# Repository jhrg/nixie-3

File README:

An alternative to the ShiftRegister74HC595 library is the builtin
shiftOut() function that is part of the Arduino IDE/libraries.

``` 
byte leds = 0;
bitSet(leds, i);

/*
 * updateShiftRegister() - This function sets the latchPin to low,
 * then calls the Arduino function 'shiftOut' to shift out contents
 * of variable 'leds' in the shift register before putting the 'latchPin' high again.
 */
void updateShiftRegister() {
    digitalWrite(latchPin, LOW);
    shiftOut(dataPin, clockPin, LSBFIRST, leds);
    digitalWrite(latchPin, HIGH);
}
```

Faster pin reads. See https://forum.arduino.cc/t/digital-read-write-pinmode-fast-execution/89116

// --- PIN MODE: OUTPUT  --- 

  DDRD |= _BV (0); // pinMode (0, OUTPUT);
  DDRD |= _BV (1); // pinMode (1, OUTPUT);
  DDRD |= _BV (2); // pinMode (2, OUTPUT);
  DDRD |= _BV (3); // pinMode (3, OUTPUT);
  DDRD |= _BV (4); // pinMode (4, OUTPUT);
  DDRD |= _BV (5); // pinMode (5, OUTPUT);
  DDRD |= _BV (6); // pinMode (6, OUTPUT);
  DDRD |= _BV (7); // pinMode (7, OUTPUT);
  DDRB |= _BV (0); // pinMode (8, OUTPUT);
  DDRB |= _BV (1); // pinMode (9, OUTPUT);
  DDRB |= _BV (2); // pinMode (10, OUTPUT);
  DDRB |= _BV (3); // pinMode (11, OUTPUT);
  DDRB |= _BV (4); // pinMode (12, OUTPUT);
  DDRB |= _BV (5); // pinMode (13, OUTPUT);
  DDRC |= _BV (0); // pinMode (A0, OUTPUT);
  DDRC |= _BV (1); // pinMode (A1, OUTPUT);
  DDRC |= _BV (2); // pinMode (A2, OUTPUT);
  DDRC |= _BV (3); // pinMode (A3, OUTPUT);
  DDRC |= _BV (4); // pinMode (A4, OUTPUT);
  DDRC |= _BV (5); // pinMode (A5, OUTPUT);

// --- PIN MODE: INPUT  --- 

  DDRD &= ~_BV (0); // pinMode (0, INPUT);
  DDRD &= ~_BV (1); // pinMode (1, INPUT);
  DDRD &= ~_BV (2); // pinMode (2, INPUT);
  DDRD &= ~_BV (3); // pinMode (3, INPUT);
  DDRD &= ~_BV (4); // pinMode (4, INPUT);
  DDRD &= ~_BV (5); // pinMode (5, INPUT);
  DDRD &= ~_BV (6); // pinMode (6, INPUT);
  DDRD &= ~_BV (7); // pinMode (7, INPUT);
  DDRB &= ~_BV (0); // pinMode (8, INPUT);
  DDRB &= ~_BV (1); // pinMode (9, INPUT);
  DDRB &= ~_BV (2); // pinMode (10, INPUT);
  DDRB &= ~_BV (3); // pinMode (11, INPUT);
  DDRB &= ~_BV (4); // pinMode (12, INPUT);
  DDRB &= ~_BV (5); // pinMode (13, INPUT);
  DDRC &= ~_BV (0); // pinMode (A0, INPUT);
  DDRC &= ~_BV (1); // pinMode (A1, INPUT);
  DDRC &= ~_BV (2); // pinMode (A2, INPUT);
  DDRC &= ~_BV (3); // pinMode (A3, INPUT);
  DDRC &= ~_BV (4); // pinMode (A4, INPUT);
  DDRC &= ~_BV (5); // pinMode (A5, INPUT);

// --- DIGITAL WRITE: HIGH  --- 

  PORTD |= _BV (0); // digitalWrite (0, HIGH);
  PORTD |= _BV (1); // digitalWrite (1, HIGH);
  PORTD |= _BV (2); // digitalWrite (2, HIGH);
  PORTD |= _BV (3); // digitalWrite (3, HIGH);
  PORTD |= _BV (4); // digitalWrite (4, HIGH);
  PORTD |= _BV (5); // digitalWrite (5, HIGH);
  PORTD |= _BV (6); // digitalWrite (6, HIGH);
  PORTD |= _BV (7); // digitalWrite (7, HIGH);

  PORTB |= _BV (0); // digitalWrite (8, HIGH);
  PORTB |= _BV (1); // digitalWrite (9, HIGH);
  PORTB |= _BV (2); // digitalWrite (10, HIGH);
  PORTB |= _BV (3); // digitalWrite (11, HIGH);
  PORTB |= _BV (4); // digitalWrite (12, HIGH);
  PORTB |= _BV (5); // digitalWrite (13, HIGH);

  PORTC |= _BV (0); // digitalWrite (A0, HIGH);
  PORTC |= _BV (1); // digitalWrite (A1, HIGH);
  PORTC |= _BV (2); // digitalWrite (A2, HIGH);
  PORTC |= _BV (3); // digitalWrite (A3, HIGH);
  PORTC |= _BV (4); // digitalWrite (A4, HIGH);
  PORTC |= _BV (5); // digitalWrite (A5, HIGH);

// --- DIGITAL WRITE: LOW  --- 

  PORTD &= ~_BV (0); // digitalWrite (0, LOW);
  PORTD &= ~_BV (1); // digitalWrite (1, LOW);
  PORTD &= ~_BV (2); // digitalWrite (2, LOW);
  PORTD &= ~_BV (3); // digitalWrite (3, LOW);
  PORTD &= ~_BV (4); // digitalWrite (4, LOW);
  PORTD &= ~_BV (5); // digitalWrite (5, LOW);
  PORTD &= ~_BV (6); // digitalWrite (6, LOW);
  PORTD &= ~_BV (7); // digitalWrite (7, LOW);

  PORTB &= ~_BV (0); // digitalWrite (8, LOW);
  PORTB &= ~_BV (1); // digitalWrite (9, LOW);
  PORTB &= ~_BV (2); // digitalWrite (10, LOW);
  PORTB &= ~_BV (3); // digitalWrite (11, LOW);
  PORTB &= ~_BV (4); // digitalWrite (12, LOW);
  PORTB &= ~_BV (5); // digitalWrite (13, LOW);
  
  PORTC &= ~_BV (0); // digitalWrite (A0, LOW);
  PORTC &= ~_BV (1); // digitalWrite (A1, LOW);
  PORTC &= ~_BV (2); // digitalWrite (A2, LOW);
  PORTC &= ~_BV (3); // digitalWrite (A3, LOW);
  PORTC &= ~_BV (4); // digitalWrite (A4, LOW);
  PORTC &= ~_BV (5); // digitalWrite (A5, LOW);

// --- DIGITAL READ  --- 

  x = (PIND & _BV (0)) == 0; // digitalRead (0);
  x = (PIND & _BV (1)) == 0; // digitalRead (1);
  x = (PIND & _BV (2)) == 0; // digitalRead (2);
  x = (PIND & _BV (3)) == 0; // digitalRead (3);
  x = (PIND & _BV (4)) == 0; // digitalRead (4);
  x = (PIND & _BV (5)) == 0; // digitalRead (5);
  x = (PIND & _BV (6)) == 0; // digitalRead (6);
  x = (PIND & _BV (7)) == 0; // digitalRead (7);
  x = (PINB & _BV (0)) == 0; // digitalRead (8);
  x = (PINB & _BV (1)) == 0; // digitalRead (9);
  x = (PINB & _BV (2)) == 0; // digitalRead (10);
  x = (PINB & _BV (3)) == 0; // digitalRead (11);
  x = (PINB & _BV (4)) == 0; // digitalRead (12);
  x = (PINB & _BV (5)) == 0; // digitalRead (13);
  x = (PINC & _BV (0)) == 0; // digitalRead (A0);
  x = (PINC & _BV (1)) == 0; // digitalRead (A1);
  x = (PINC & _BV (2)) == 0; // digitalRead (A2);
  x = (PINC & _BV (3)) == 0; // digitalRead (A3);
  x = (PINC & _BV (4)) == 0; // digitalRead (A4);
  x = (PINC & _BV (5)) == 0; // digitalRead (A5);

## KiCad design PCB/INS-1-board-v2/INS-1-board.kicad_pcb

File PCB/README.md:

## Ideal Project Structure

    my_kicad_project/
    ├── my_project.kicad_sch
    ├── my_project.kicad_pcb
    ├── my_project.kicad_pro
    ├── footprints/
    │   └── custom_footprint.pretty/
    └── symbols/
        └── custom_symbol.kicad_sym

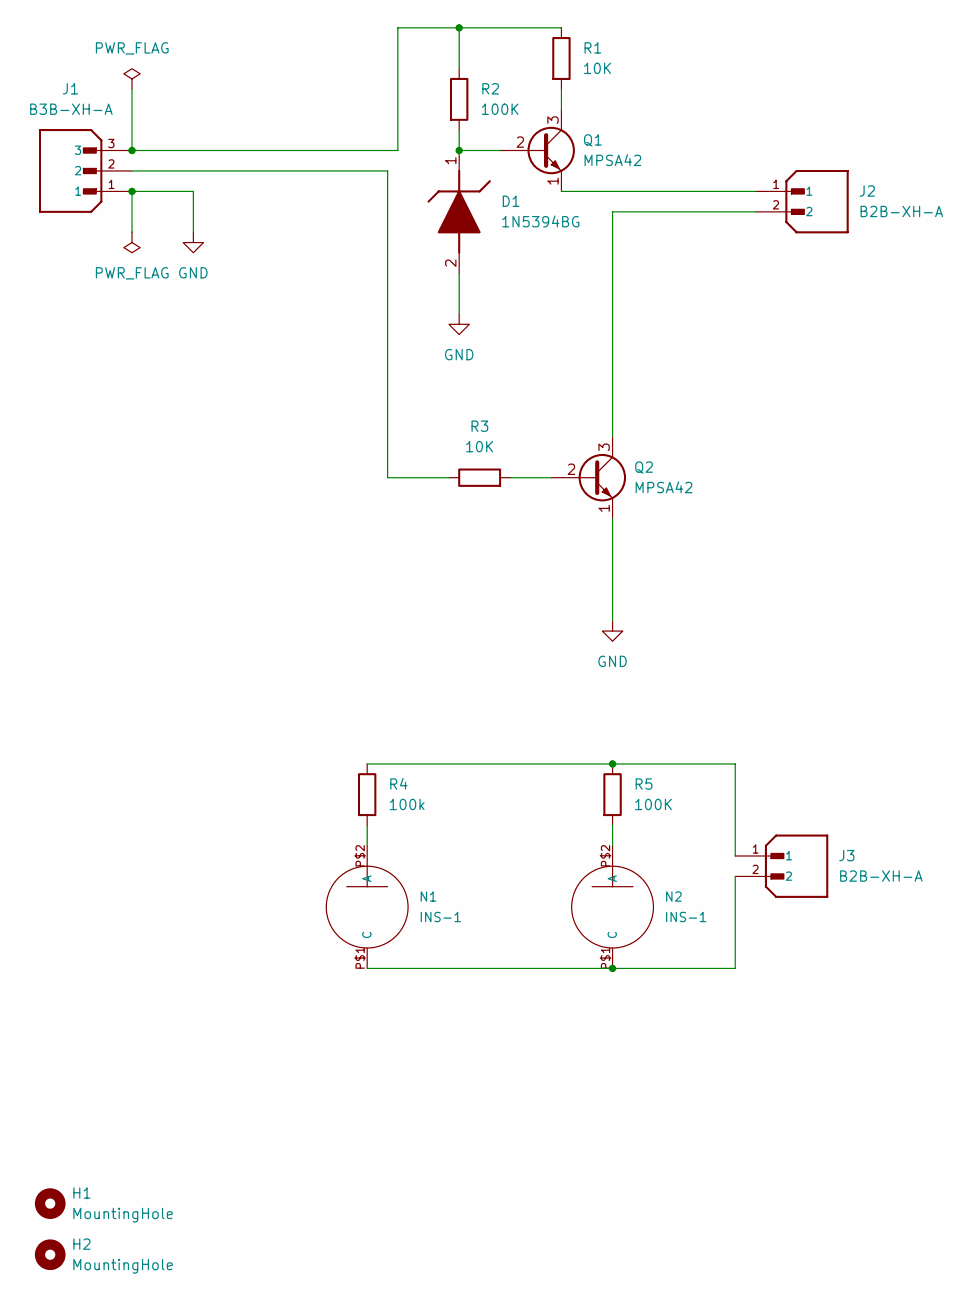
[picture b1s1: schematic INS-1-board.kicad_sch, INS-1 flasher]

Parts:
D1: 1N5394BG; DIOAD2260W109L864D349; Manufacturer_Part_Number 1N5374BG
H1, H2: MountingHole; MountingHole_2.7mm
J1: B3B-XH-A; JST_B3B-XH-A; PARTREV 7/4/21
J2, J3: B2B-XH-A; JST_B2B-XH-A; PARTREV N/A
N1, N2: INS-1; mynixies-INS-1
Q1, Q2: MPSA42; TO-92L_HandSolder
R1, R3: 10K; R_Axial_DIN0207_L6.3mm_D2.5mm_P7.62mm_Horizontal
R2, R5: 100K; R_Axial_DIN0207_L6.3mm_D2.5mm_P7.62mm_Horizontal
R4: 100k; R_Axial_DIN0207_L6.3mm_D2.5mm_P7.62mm_Horizontal

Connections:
GND: D1.2 (A), J1.1, Q2.1 (E)
unnamed: D1.1 (K), Q1.2 (B), R2.2
unnamed: J1.2, R3.1
unnamed: J1.3, R1.1, R2.1
unnamed: J3.1, R4.1, R5.1
unnamed: N1.P$2 (A), R4.2
unnamed: J3.2, N1.P$1 (C), N2.P$1 (C)
unnamed: N2.P$2 (A), R5.2
unnamed: Q1.3 (C), R1.2
unnamed: J2.1, Q1.1 (E)
unnamed: Q2.2 (B), R3.2
unnamed: J2.2, Q2.3 (C)

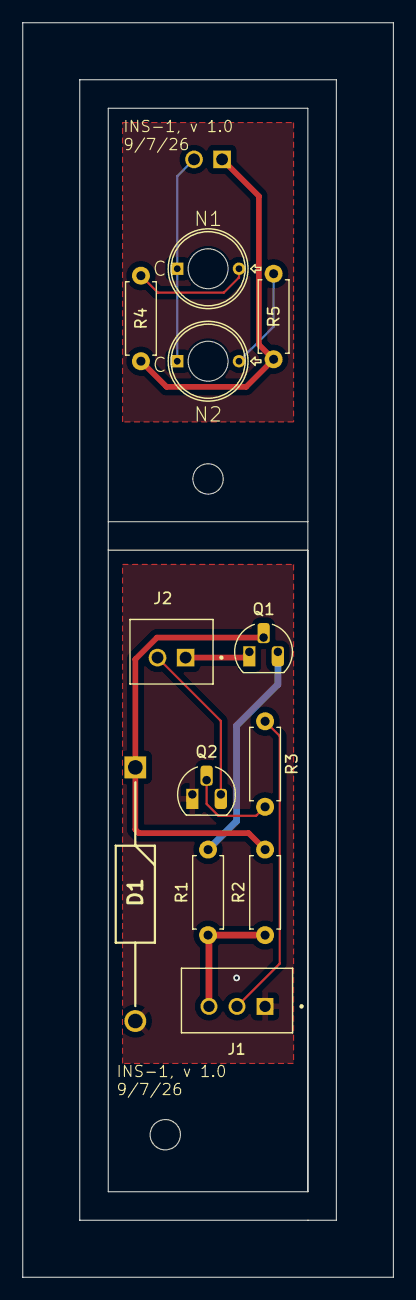
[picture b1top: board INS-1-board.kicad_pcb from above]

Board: 2 copper layers, 33.0 x 111.8 mm, 15 parts (1 on the bottom side), 12 nets.

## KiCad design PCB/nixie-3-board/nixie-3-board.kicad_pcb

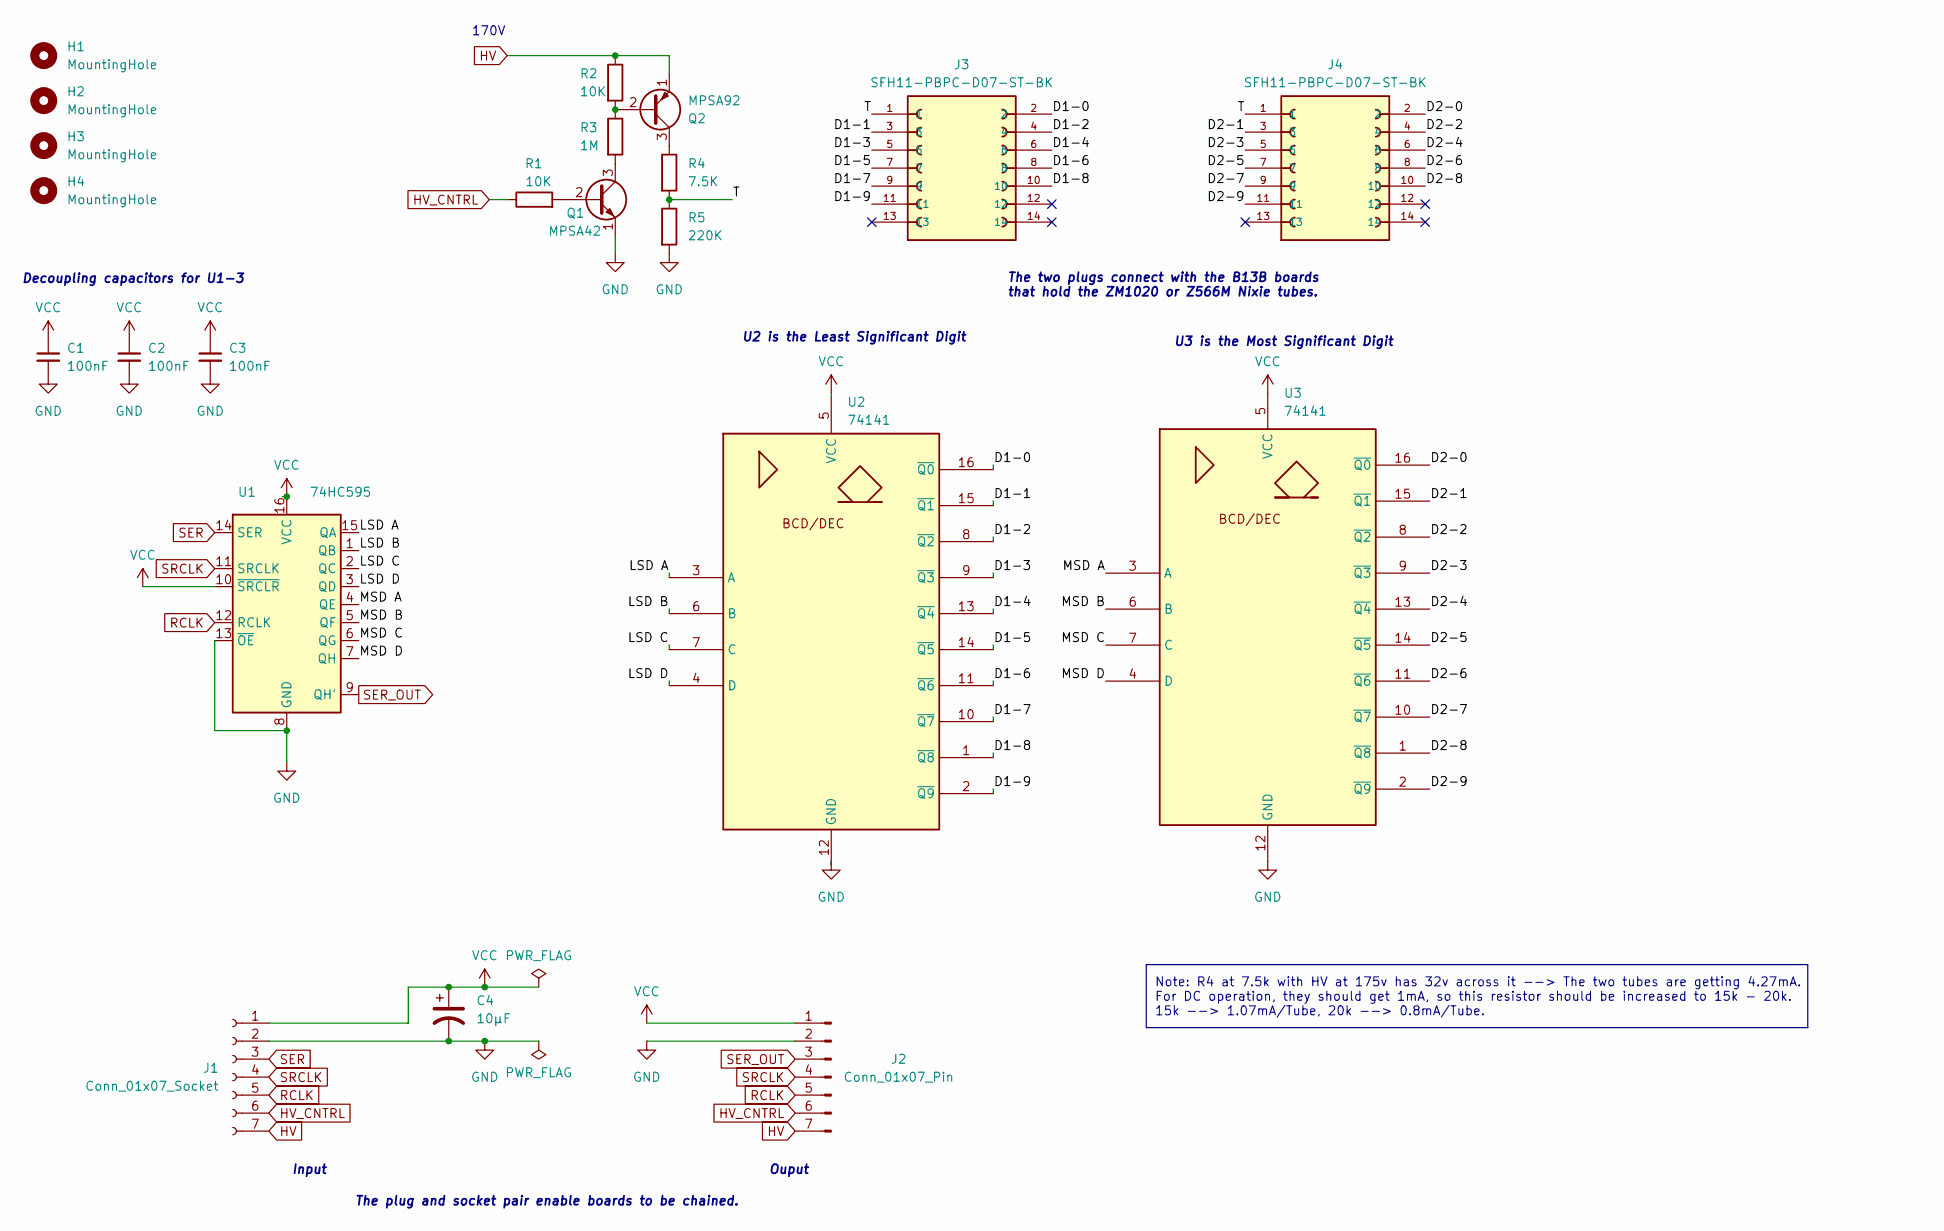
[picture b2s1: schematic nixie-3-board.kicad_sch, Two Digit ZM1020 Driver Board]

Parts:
C1, C2, C3: 100nF; K104Z15Y5VF5TL2_VIS
C4: 10µF; U1-E_NCH
H1, H2, H3, H4: MountingHole; MountingHole_2.7mm_M2.5_DIN965
J1: Conn_01x07_Socket; PinSocket_1x07_P2.54mm_Horizontal
J2: Conn_01x07_Pin; PinHeader_1x07_P2.54mm_Horizontal
J3, J4: SFH11-PBPC-D07-ST-BK; SULLINS_SFH11-PBPC-D07-ST-BK; PARTREV J
Q1: MPSA42; TO-92_HandSolder
Q2: MPSA92; TO-92_HandSolder
R1, R2: 10K; R_Axial_DIN0207_L6.3mm_D2.5mm_P7.62mm_Horizontal
R3: 1M; R_Axial_DIN0207_L6.3mm_D2.5mm_P7.62mm_Horizontal
R4: 7.5K; R_Axial_DIN0207_L6.3mm_D2.5mm_P7.62mm_Horizontal
R5: 220K; R_Axial_DIN0207_L6.3mm_D2.5mm_P7.62mm_Horizontal
U1: 74HC595; DIP-16_W7.62mm_Socket
U2, U3: 74141; DIP-16_W7.62mm_Socket

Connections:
/D1-0: J3.2, U2.16 (~Q0)
/D1-1: J3.3, U2.15 (~Q1)
/D1-2: J3.4, U2.8 (~Q2)
/D1-3: J3.5, U2.9 (~Q3)
/D1-4: J3.6, U2.13 (~Q4)
/D1-5: J3.7, U2.14 (~Q5)
/D1-6: J3.8, U2.11 (~Q6)
/D1-7: J3.9, U2.10 (~Q7)
/D1-8: J3.10, U2.1 (~Q8)
/D1-9: J3.11, U2.2 (~Q9)
/D2-0: J4.2, U3.16 (~Q0)
/D2-1: J4.3, U3.15 (~Q1)
/D2-2: J4.4, U3.8 (~Q2)
/D2-3: J4.5, U3.9 (~Q3)
/D2-4: J4.6, U3.13 (~Q4)
/D2-5: J4.7, U3.14 (~Q5)
/D2-6: J4.8, U3.11 (~Q6)
/D2-7: J4.9, U3.10 (~Q7)
/D2-8: J4.10, U3.1 (~Q8)
/D2-9: J4.11, U3.2 (~Q9)
/LSD A: U1.15 (QA), U2.3 (A)
/LSD B: U1.1 (QB), U2.6 (B)
/LSD C: U1.2 (QC), U2.7 (C)
/LSD D: U1.3 (QD), U2.4 (D)
/MSD A: U1.4 (QE), U3.3 (A)
/MSD B: U1.5 (QF), U3.6 (B)
/MSD C: U1.6 (QG), U3.7 (C)
/MSD D: U1.7 (QH), U3.4 (D)
/T: J3.1, J4.1, R4.2, R5.1
GND: C1.2, C2.2, C3.2, C4.2, J1.2, J2.2, Q1.1 (E), R5.2, U1.8 (GND), U1.13 (~OE), U2.12 (GND), U3.12 (GND)
HV: J1.7, J2.7, Q2.1 (E), R2.1
HV_CNTRL: J1.6, J2.6, R1.1
unnamed: Q1.2 (B), R1.2
unnamed: Q1.3 (C), R3.2
unnamed: Q2.2 (B), R2.2, R3.1
unnamed: Q2.3 (C), R4.1
RCLK: J1.5, J2.5, U1.12 (RCLK)
SER: J1.3, U1.14 (SER)
SER_OUT: J2.3, U1.9 (QH')
SRCLK: J1.4, J2.4, U1.11 (SRCLK)
VCC: C1.1, C2.1, C3.1, C4.1, J1.1, J2.1, U1.10 (~SRCLR), U1.16 (VCC), U2.5 (VCC), U3.5 (VCC)

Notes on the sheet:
U2 is the Least Significant Digit
Ouput
The plug and socket pair enable boards to be chained.
170V
Note: R4 at 7.5k with HV at 175v has 32v across it --> The two tubes are getting 4.27mA. For DC operation, they should get 1mA, so this resistor should be increased to 15k - 20k. 15k --> 1.07mA/Tube, 20k --> 0.8mA/Tube.
U3 is the Most Significant Digit
The two plugs connect with the B13B boards that hold the ZM1020 or Z566M Nixie tubes.
Input
Decoupling capacitors for U1-3

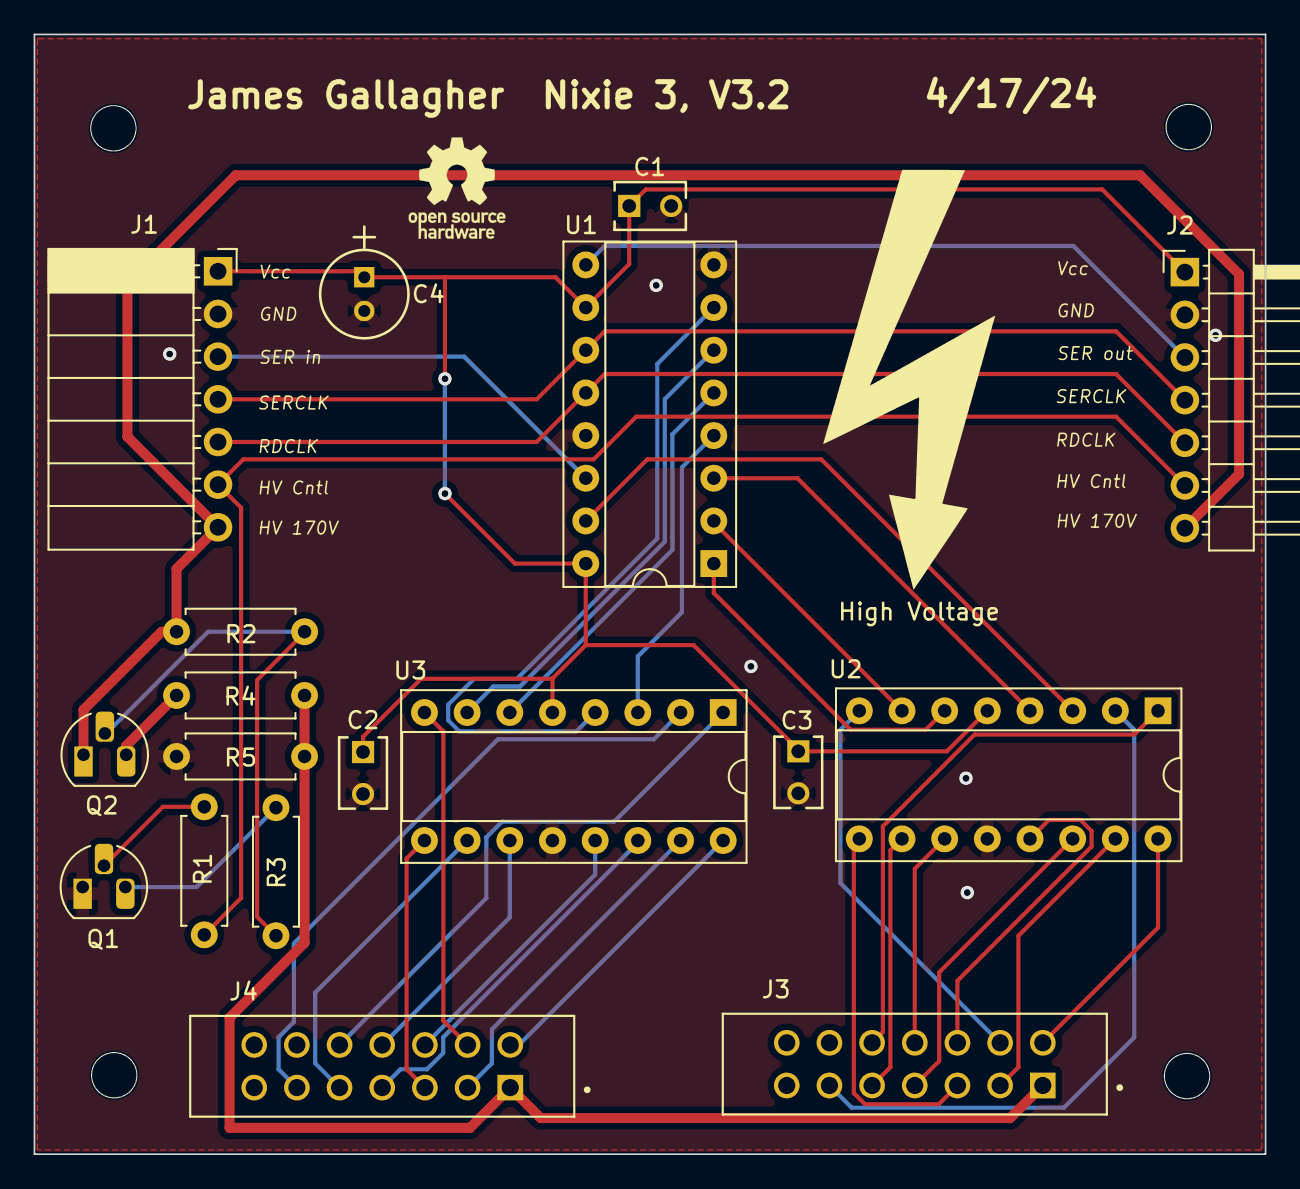
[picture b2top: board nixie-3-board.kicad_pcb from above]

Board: 2 copper layers, 73.3 x 66.6 mm, 22 parts (0 on the bottom side), 41 nets.

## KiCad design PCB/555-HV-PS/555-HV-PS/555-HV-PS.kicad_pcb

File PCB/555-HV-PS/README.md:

# 555 HV Power supply for Nixie tubes

This is a power supply for nixie tubes based on the 555 timer chip. The 555 is configured in its astable mode with a frequency of ~32kHz.

When I used this, it has some ripple in the output and there is some slight ghosting of the digits that I think is from noise affecting the serial output to the nixie 3.2 driver board. When I use a commercial supply that has cleaner output, there is no ghosting. However, it might be that noise from my breadboard version of the HV PS is the problem and not the output itself.

## About the RC snubber

R5 and C9 are a RC snubber to limit ringing at the from Q2 when it switches off. 
In these images, yellow is the hig voltage at the inductor-diode-Q2 junction or the
HV output of the PS and magenta is the switching voltage from pin 3 of the 555 (i.e.,
the gate of Q2).

Without the RC snubber, there is ringing when Q2 turns off:

The snubber circuit can damp this ringing - that might help clean up the output.
Here are the effects of various values of R5 and C9. I choose R5 at 15k and C9
as 100pF initially based on info from [DigiKey's article on RC snubbers for power switches](https://www.digikey.com/en/articles/resistor-capacitor-rc-snubber-design-for-power-switches).

Some improvement.

Dropping R5 down to 1K makes a bigger difference, but the efficiency of the PS
drops (the current draw goes from 370mA to 400mA):

Increasing C9 to 470pF makes an even bigger improvement, but the PS is still drawing 400mA
@12V from the bench supply:

Increasing R5 to 3.3K reduces the power needed (back to 370mA @12V) with decent damping:

The output of the PS looks like:

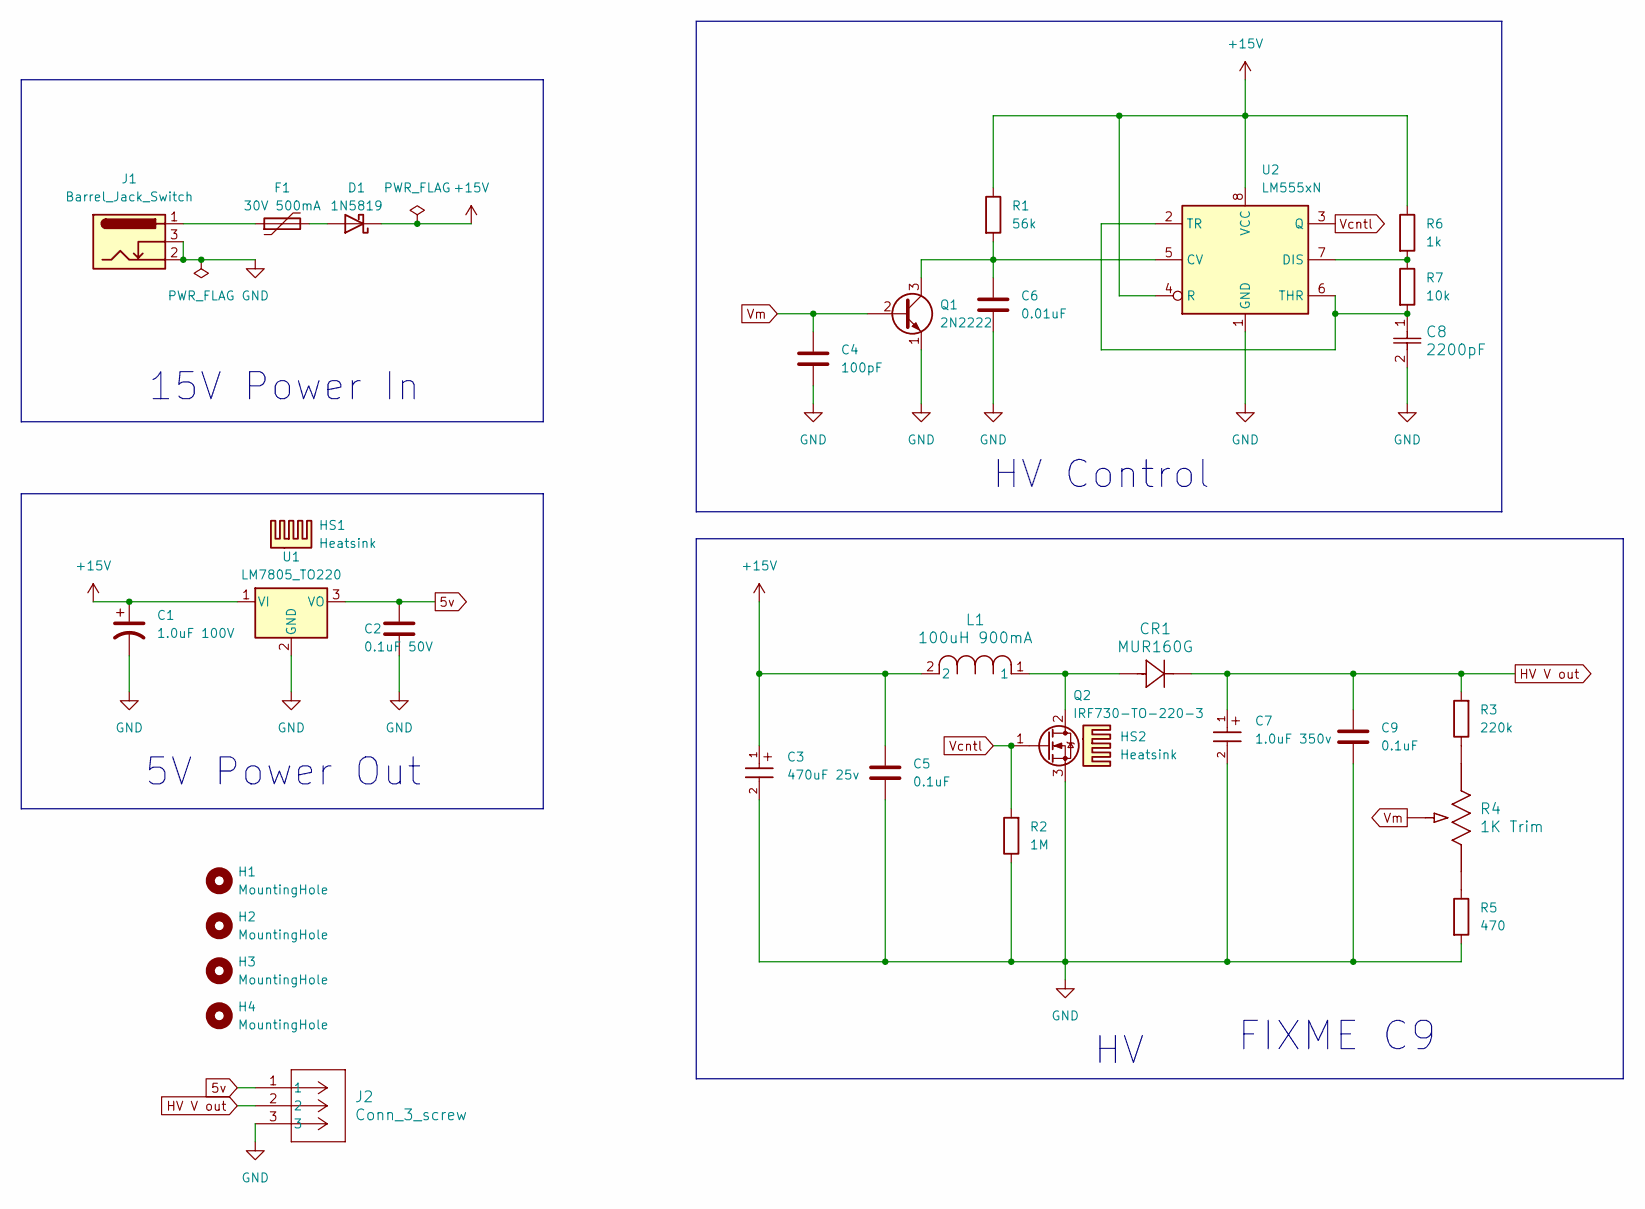
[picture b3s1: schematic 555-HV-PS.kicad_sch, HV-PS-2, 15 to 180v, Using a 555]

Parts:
C1: 1.0uF 100V; 1.0uF_160V_CAPPRD200W50D525H1250
C2: 0.1uF 50V; C_Disc_D5.0mm_W2.5mm_P5.00mm
C3: 470uF 25v; WCAP-ATUL_10X16_DXL_470uF-25v
C4: 100pF; C_Disc_D4.3mm_W1.9mm_P5.00mm
C5, C9: 0.1uF; C_Disc_D5.0mm_W2.5mm_P5.00mm
C6: 0.01uF; C_Disc_D4.3mm_W1.9mm_P5.00mm
C7: 1.0uF 350v; WCAP-ATET_8X11.5_DXL_
C8: 2200pF; CAP_S-SERIES_N-29-J_VIS
CR1: MUR160G
D1: 1N5819; D_DO-41_SOD81_P10.16mm_Horizontal
F1: 30V 500mA; AHRF050_30v_500mA_polyfuse
H1, H2, H3, H4: MountingHole; MountingHole_3mm
HS1, HS2: Heatsink; AVVID-577202B-00000G
J1: Barrel_Jack_Switch; BarrelJack_Horizontal
J2: Conn_3_screw; CONN3_OSTVN03A150_OST
L1: 100uH 900mA; IND_8095-WE-TI_8p3x10x5_WRE
Q1: 2N2222; TO-92_Inline
Q2: IRF730-TO-220-3; TO-220-3_Vertical
R1: 56k; R_Axial_DIN0207_L6.3mm_D2.5mm_P10.16mm_Horizontal
R2: 1M; R_Axial_DIN0207_L6.3mm_D2.5mm_P10.16mm_Horizontal
R3: 220k; R_Axial_DIN0207_L6.3mm_D2.5mm_P10.16mm_Horizontal
R4: 1K Trim; 10k_Trimmer_PV36W103C01B00
R5: 470; R_Axial_DIN0207_L6.3mm_D2.5mm_P10.16mm_Horizontal
R6: 1k; R_Axial_DIN0207_L6.3mm_D2.5mm_P10.16mm_Horizontal
R7: 10k; R_Axial_DIN0207_L6.3mm_D2.5mm_P10.16mm_Horizontal
U1: LM7805_TO220; TO-220-3_Vertical
U2: LM555xN; DIP-8_W7.62mm

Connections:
5v: C2.1, J2.1, U1.3 (VO)
+15V: C1.1, C3.1, C5.1, D1.1 (K), L1.2, R1.1, R6.1, U1.1 (VI), U2.4 (R), U2.8 (VCC)
GND: C1.2, C2.2, C3.2, C4.2, C5.2, C6.2, C7.2, C8.2, C9.2, J1.2, J1.3, J2.3, Q1.1 (E), Q2.3 (S), R2.1, R5.2, U1.2 (GND), U2.1 (GND)
HV V out: C7.1, C9.1, CR1.1, J2.2, R3.2
unnamed: D1.2 (A), F1.2
unnamed: F1.1, J1.1
unnamed: C6.1, Q1.3 (C), R1.2, U2.5 (CV)
unnamed: CR1.2, L1.1, Q2.2 (D)
unnamed: R3.1, R4.3
unnamed: R4.1, R5.1
unnamed: R6.2, R7.1, U2.7 (DIS)
unnamed: C8.1, R7.2, U2.2 (TR), U2.6 (THR)
Vcntl: Q2.1 (G), R2.2, U2.3 (Q)
Vm: C4.1, Q1.2 (B), R4.2

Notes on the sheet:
FIXME C9
15V Power In
HV Control
5V Power Out

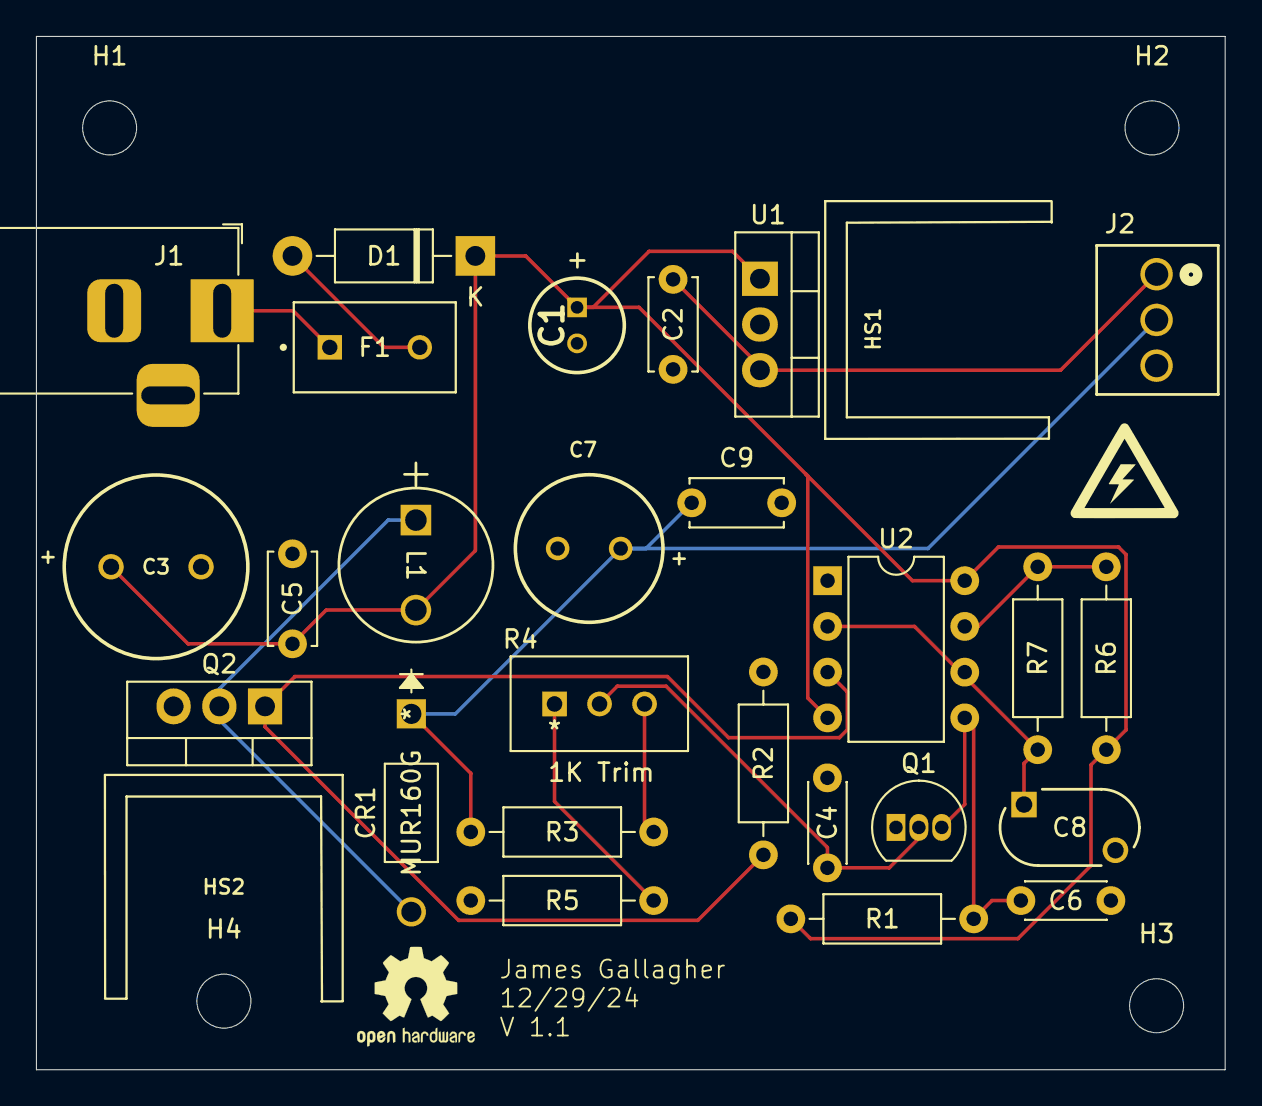
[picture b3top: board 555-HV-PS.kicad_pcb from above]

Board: 2 copper layers, 66.0 x 57.4 mm, 32 parts (0 on the bottom side), 14 nets.

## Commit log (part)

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2023-10-22 Added .gitignore
2023-10-23 Updates: Added ShiftRegister74HC595, print.cc and modde_switch.cc
2023-10-23 Fixed the dimming feature
    The mode switch code and brightness control are now
    held in mode_switch.cc There is no need to poll the
    input switch. Instead the callback updates the brightness.
2023-10-24 Changed the values for brightness. 50% duty cycle is just barely noticable.
2023-10-24 Added a blankout brightness level
2024-01-03 Added more stuff for PCB abd added docs
2024-01-04 new layout - might work. Needs holes, markings, screw terminals
2024-02-11 Version 3 of the driver PCB
    Adds decouping caps and re-orders digits so LSD is on the right.
2024-02-11 Added capacitor footprints
2024-02-11 Fixed mistakes, v3.1
2024-02-12 Better names for the decoupling cap footprint files
    Also corrected the value for the PS decoupling cap from 100uF to 10uF
2024-04-10 Use new board version
2024-04-18 Added second set of digits
2024-04-18 Added high voltage symbol to display PCB
2024-04-18 Graphics
2024-08-08 Added RTC and display of the time
2024-08-10 Fixed the 1Hz ISR so that only one of update_time or get_time is true.
    The ISR was written so that when get_time was true, update_time
    was also true. That caused the time to be updated twice and which
    made for a glitch once every few minutes where the time would advance
    only to be reset a moment later (because code that polls the flags
    set by the ISR runs very often).
2024-08-31 Removed an object copy from print_time() debug function
2024-08-31 Added HV PS Test program using a pio environment
2024-08-31 Ignore emacs backup files
2024-09-01 Needed to set pin 10 as output - fixed using hv_ps_test.cc
2024-09-01 How often hv_ps_adjust() affects output stability. Why?
2024-09-04 Use the HV PS driven by the arduino PWM signal.
2024-09-05 Change the main loop and DEBUG switch
2024-09-07 Dropped the ShiftRegister74HC595 library, other tweaks.
2024-09-07 Comments
2024-09-14 Flashes separtor for seconds
2024-09-15 Removed HV PS PID controller and added a flashing colon.
    Should have been two branches. Anyway, the PID controller is gone.
    Use a dedicated HV PS that does not need the MCU.
    Added a flashing colon and simplified the use of the clock. There
    seems to be no need to limit the use of the I2C bus to read from the
    DS3231 to once every 10s; it seems to be fine to read every second.
2024-09-15 Retired the HV PS code, removed unused libs, added KiCAD files
2024-09-15 Removed more unused code
2024-09-15 Use fast writes for separator
2024-12-30 Removed unused INPUT_SWITCH, dropped PORTB use by the RTC
2024-12-31 Added PCB files for the HV PS and INS tube circuits
2024-12-31 Added to .gitignore
2024-12-31 Moved more stuff around in the 555 HV PS subdirs
2024-12-31 More 55 HV PS files
2024-12-31 Most of the switch #define for pins and a single pin def header is complete
2024-12-31 Clean up changes - remove unused code.
2025-01-04 The HH:MM and MM:SS modes work - 2s+ mode switch (but < 5s)
2025-01-20 New mode switching code.
2025-03-15 Fixed some include issues.
2025-07-02 KiCAD updates for version 8
2025-07-02 Added INS-1-board-v2.zip
2025-07-02 Create README-zener.md
    Does the markup work? Pretty much straight from ChatGPT.
2025-07-06 Edits to the 555 HV PS circuit and added some info
    I added a README to the PCB/555-HV-PS directory with some
    images from the ocilloscope.
2025-07-06 Moved old INS-1 board to retired and updated INS-1 v2 board.
2025-07-06 Board update
2025-07-16 Add PWM dimming for the INS-1 colon.
2025-07-16 Added INS-1-v2 schematic and board
2025-07-16 Minor fix to zener readme
2025-07-16 Updated some comments and the mode_switch2 setup()
2025-07-29 Initial version of mode switch on pin 6
2025-07-29 Resolved conflicts
2025-07-30 Added a second button switch.
2025-08-31 minor edits to comments
2026-02-28 Comment fix to main.cpp

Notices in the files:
parts and their libraries:
Copyright 2021 Accelerated Designs. All rights reserved.
